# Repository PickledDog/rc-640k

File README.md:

# rc-640k
 128K+512K RAM/ROM card for RC2014

## Overview
This RC2014-compatible board provides RAM and flash ROM, software-pageable in 32k pages. 16 ROM or 4 RAM pages may be paged into the lower 32k of Z80 memory. This paging scheme is compatible with Wayne Warthen's [RomWBW](https://github.com/wwarthen/RomWBW).

## Memory details
For ROM, a SST39SF040 512k x 8 flash chip is used. It can be programmed in-place using Will Sowerbutts' FLASH4 utility (included with RomWBW). For RAM, an AS6C1008 128k x 8 SRAM is used, providing 128K of addressable memory. Both are divided into 32k pages, and any page of either chip can be paged into the lower 32k of the address space. The upper 32k is permanently mapped to the last page of the RAM chip.

## Paging
Upon reset, the first page of the ROM is mapped to the lower 32k. If left alone, the board will behave like any 32k ROM+32k RAM RC2014 system. A config register is used to set the currently mapped page, presented as an I/O device at 0x78 (the address used by most "large" Z80 memory systems). The low nibble sets the page number (0-15 for ROM, 0-3 for RAM), and high bit 7 selects the chip (0 for ROM, 1 for RAM).

The port address and layout are chosen to be (mostly) compatible with the [RetroBrew SBC](https://www.retrobrewcomputers.org/doku.php?id=boards:sbc:sbc_v2:sbc_v2-003). The SBC has separate ROM and RAM registers (on 0x78 and 0x7C); this board uses a single register for both, which can be written to from either address.

## Firmware
Many [RC2014 ROM images](https://github.com/RC2014Z80/RC2014/tree/master/ROMs) can be used (selecting the right image for your serial board), but some will require modification to accommodate the different paging system. The 32k BASIC images work unmodified. Stephen C Cousins' excellent [Small Computer Monitor](https://smallcomputercentral.wordpress.com/small-computer-monitor/) can be used as well - choose the R3 configuration. CP/M loading *won't work* without code changes.

But most importantly, this board is compatible with [RomWBW](https://github.com/wwarthen/RomWBW), providing several CP/M versions, ROM applications, and maximized free application memory. It will need to be built from source with configuration changes, although this is fairly straightforward (RomWBW includes its entire build toolchain in the source tree). The build process is covered in [this page](https://github.com/wwarthen/RomWBW/blob/master/Source/ReadMe.txt) from the RomWBW documentation (including Linux and Mac instructions). An example image can be found in the [firmware](/firmware) directory.

### RomWBW Config changes
With the [source tree](https://github.com/wwarthen/RomWBW) unpacked, go into `Source/HBIOS/Config` and make a copy of `RCZ80_std.asm` (call it `RCZ80_pd.asm`). Edit this new file, and add the following lines:
```
RAMSIZE		.SET	128		; SIZE OF RAM IN KB (MUST MATCH YOUR HARDWARE!!!)
MEMMGR		.SET	MM_SBC		; MEMORY MANAGER: MM_[SBC|Z2|N8|Z180]
MPCL_RAM	.EQU	$78		; SBC MEM MGR RAM PAGE SELECT REG (WRITE ONLY)
MPCL_ROM	.EQU	$7C		; SBC MEM MGR ROM PAGE SELECT REG (WRITE ONLY)
;
```
As of RomWBW 3.1, it is possible to have a ROMdisk without a RAMdisk (which this board does not support). If building RomWBW 3.1 or later, add this line too: 
```
MDRAM		.SET	FALSE		; MD: DISABLE RAM DISK
;
```
With our new file, we can go ahead and build our ROM image. Under Windows, this is done with the following commands in `Source`:

* `BuildShared`
  * Wait for this to complete, ignoring the harmless program origin warnings
* `BuildROM`
  * Enter `RCZ80` at the *Platform* prompt
  * Enter `pd` at the *Configuration* prompt

Once the build is complete, we are done! Back at the root of the source tree, go into `Binary` and retrieve our new `RCZ80_pd.rom`. This can now be burned to the flash chip using an EPROM programmer, such as a [TL866](https://www.ebay.com/sch/i.html?_nkw=tl866ii+plus).

## Part selection
Bill Of Materials and part references are below. I recommend using gold-plated header for the bus connection - I use these ones from [Pololu](https://www.pololu.com/product/967) or [Sparkfun](https://www.sparkfun.com/products/553). A nice detail of these, is that they sit at the same height as double-row header in a backplane.

The specified parts are just the ones I used, and can be substituted as needed - Mouser links provided for convenience and reference.

| Reference | Value | Qty | Mouser link |
| --------- | ----- | --- | ----------- |
| C1-C5 | 100nF ceramic | 5 | [KEMET C315C104M5U5TA](https://www.mouser.com/ProductDetail/C315C104M5U5TA7303) |
| J1 | 1x40 right-angle header | 1 | [Wurth 61304011021](https://www.mouser.com/ProductDetail/61304011021) |
| U1 | SST39SF040 NOR flash | 1 | [Microchip SST39SF040-70-4C-PHE](https://www.mouser.com/ProductDetail/SST39SF040-70-4C-PHE) |
| U2 | AS6C1008 SRAM | 1 | [Alliance AS6C1008-55PCN](https://www.mouser.com/ProductDetail/AS6C1008-55PCN) |
| | sockets | 2 | [Amphenol DILB32P-223TLF](https://www.mouser.com/ProductDetail/DILB32P-223TLF) |
| U3 | 74HCT688 | 1 | [TI CD74HCT688E](https://www.mouser.com/ProductDetail/CD74HCT688E) |
| U4 | 74HCT174 | 1 | [TI CD74HCT174E](https://www.mouser.com/ProductDetail/CD74HCT174E) |
| U5 | 74HCT32 | 1 | [TI SN74HCT32N](https://www.mouser.com/ProductDetail/SN74HCT32N) |

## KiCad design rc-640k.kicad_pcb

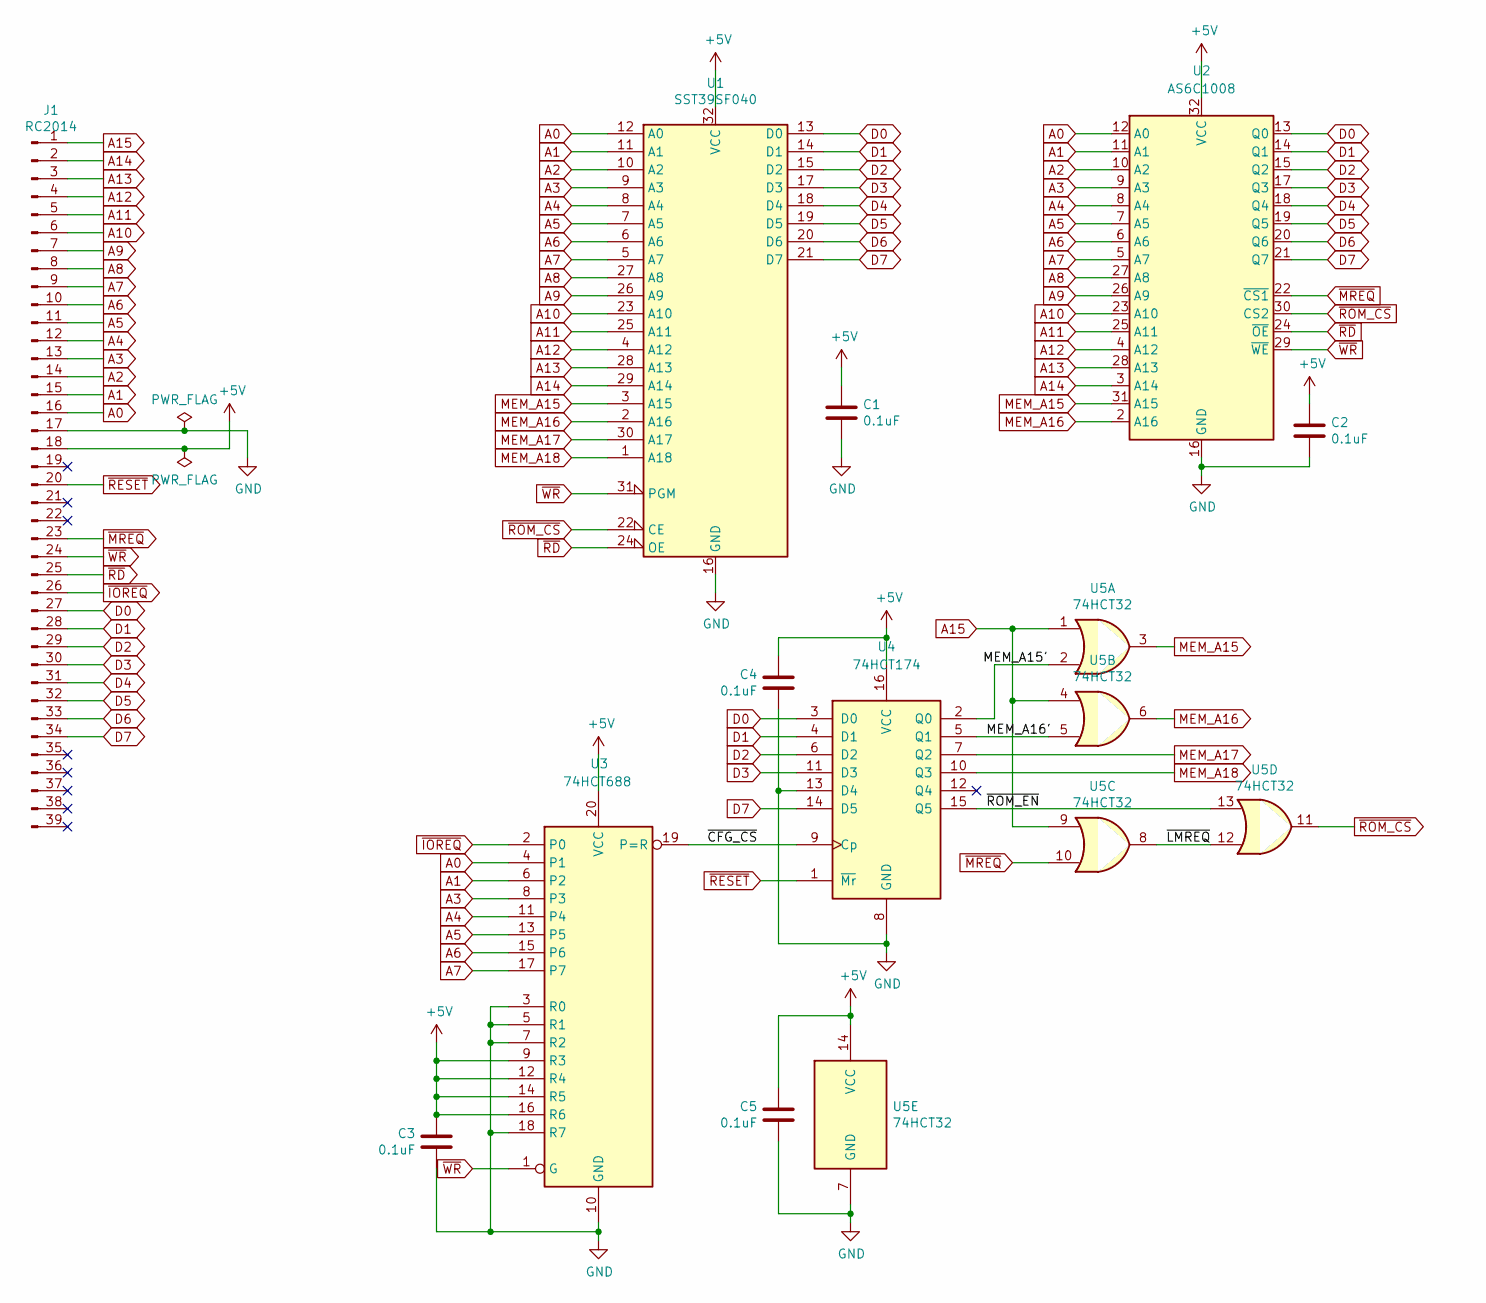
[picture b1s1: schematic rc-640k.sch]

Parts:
C1, C2, C3, C4, C5: 0.1uF; C_Disc_D3.0mm_W1.6mm_P2.50mm
J1: RC2014; PinHeader_1x39_P2.54mm_Vertical
U1: SST39SF040; DIP-32_W15.24mm_LongPads
U2: AS6C1008; DIP-32_W15.24mm_LongPads
U3: 74HCT688; DIP-20_W7.62mm_LongPads
U4: 74HCT174; DIP-16_W7.62mm_LongPads
U5: 74HCT32; DIP-14_W7.62mm_LongPads

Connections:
+5V: C1.1, C2.1, C3.2, C4.2, C5.2, J1.18, U1.32 (VCC), U2.32 (VCC), U3.9 (R3), U3.12 (R4), U3.14 (R5), U3.16 (R6), U3.20 (VCC), U4.16 (VCC), U5.14 (VCC)
/MEM_A15': U4.2 (Q0), U5.2
/MEM_A16': U4.5 (Q1), U5.5
/~CFG_CS: U3.19 (P=R), U4.9 (Cp)
/~LMREQ: U5.8, U5.12
/~ROM_EN: U4.15 (Q5), U5.13
A0: J1.16, U1.12 (A0), U2.12 (A0), U3.4 (P1)
A1: J1.15, U1.11 (A1), U2.11 (A1), U3.6 (P2)
A2: J1.14, U1.10 (A2), U2.10 (A2)
A3: J1.13, U1.9 (A3), U2.9 (A3), U3.8 (P3)
A4: J1.12, U1.8 (A4), U2.8 (A4), U3.11 (P4)
A5: J1.11, U1.7 (A5), U2.7 (A5), U3.13 (P5)
A6: J1.10, U1.6 (A6), U2.6 (A6), U3.15 (P6)
A7: J1.9, U1.5 (A7), U2.5 (A7), U3.17 (P7)
A8: J1.8, U1.27 (A8), U2.27 (A8)
A9: J1.7, U1.26 (A9), U2.26 (A9)
A10: J1.6, U1.23 (A10), U2.23 (A10)
A11: J1.5, U1.25 (A11), U2.25 (A11)
A12: J1.4, U1.4 (A12), U2.4 (A12)
A13: J1.3, U1.28 (A13), U2.28 (A13)
A14: J1.2, U1.29 (A14), U2.3 (A14)
A15: J1.1, U5.1, U5.4, U5.9
D0: J1.27, U1.13 (D0), U2.13 (Q0), U4.3 (D0)
D1: J1.28, U1.14 (D1), U2.14 (Q1), U4.4 (D1)
D2: J1.29, U1.15 (D2), U2.15 (Q2), U4.6 (D2)
D3: J1.30, U1.17 (D3), U2.17 (Q3), U4.11 (D3)
D4: J1.31, U1.18 (D4), U2.18 (Q4)
D5: J1.32, U1.19 (D5), U2.19 (Q5)
D6: J1.33, U1.20 (D6), U2.20 (Q6)
D7: J1.34, U1.21 (D7), U2.21 (Q7), U4.14 (D5)
GND: C1.2, C2.2, C3.1, C4.1, C5.1, J1.17, U1.16 (GND), U2.16 (GND), U3.3 (R0), U3.5 (R1), U3.7 (R2), U3.10 (GND), U3.18 (R7), U4.8 (GND), U4.13 (D4), U5.7 (GND)
MEM_A15: U1.3 (A15), U2.31 (A15), U5.3
MEM_A16: U1.2 (A16), U2.2 (A16), U5.6
MEM_A17: U1.30 (A17), U4.7 (Q2)
MEM_A18: U1.1 (A18), U4.10 (Q3)
~IOREQ: J1.26, U3.2 (P0)
~MREQ: J1.23, U2.22 (~CS1), U5.10
~RD: J1.25, U1.24 (OE), U2.24 (~OE)
~RESET: J1.20, U4.1 (~Mr)
~ROM_CS: U1.22 (CE), U2.30 (CS2), U5.11
~WR: J1.24, U1.31 (PGM), U2.29 (~WE), U3.1 (G)

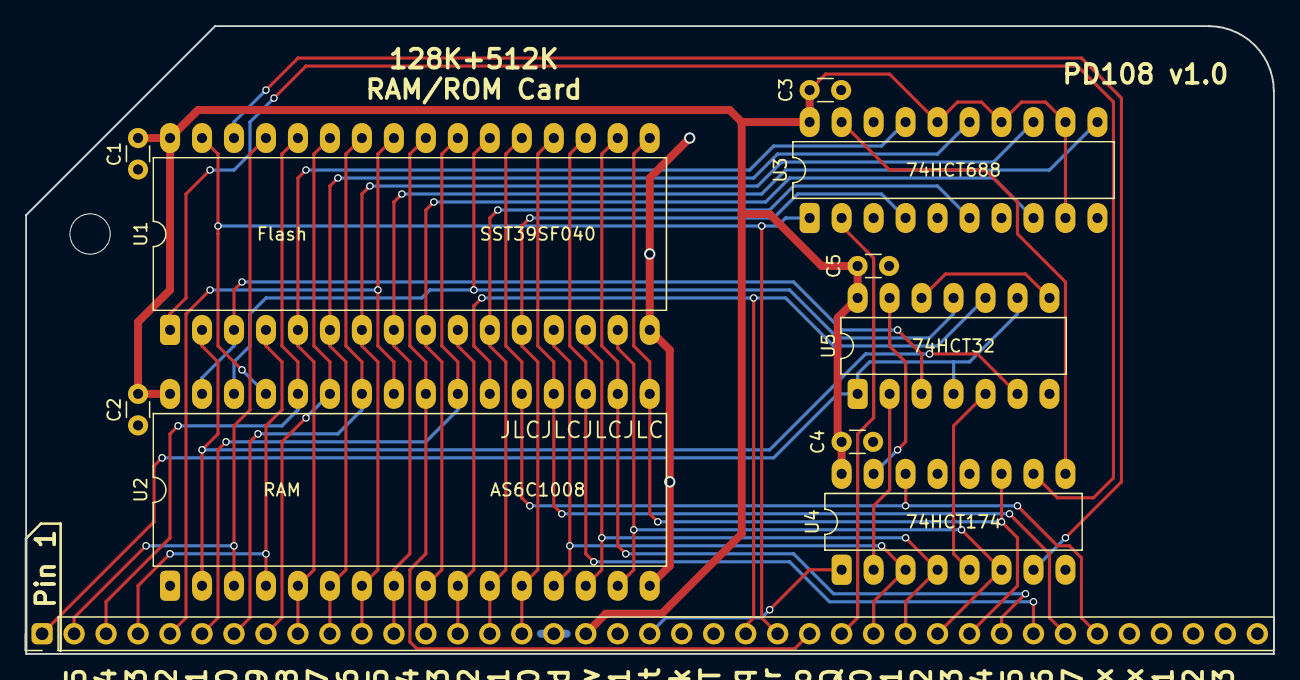
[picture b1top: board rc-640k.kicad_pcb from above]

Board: 2 copper layers, 99.1 x 49.9 mm, 11 parts (0 on the bottom side), 41 nets.

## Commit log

2021-02-15 Initial commit of rc-640k/PD108
2021-02-18 Move to v1.0
    Neaten up board, improve ground plane
2021-02-20 Tweak routing
2021-02-20 Add README
2021-03-16 Update picture to current version
2021-03-27 Add note to disable RAM disk
2021-04-20 Add example firmware
